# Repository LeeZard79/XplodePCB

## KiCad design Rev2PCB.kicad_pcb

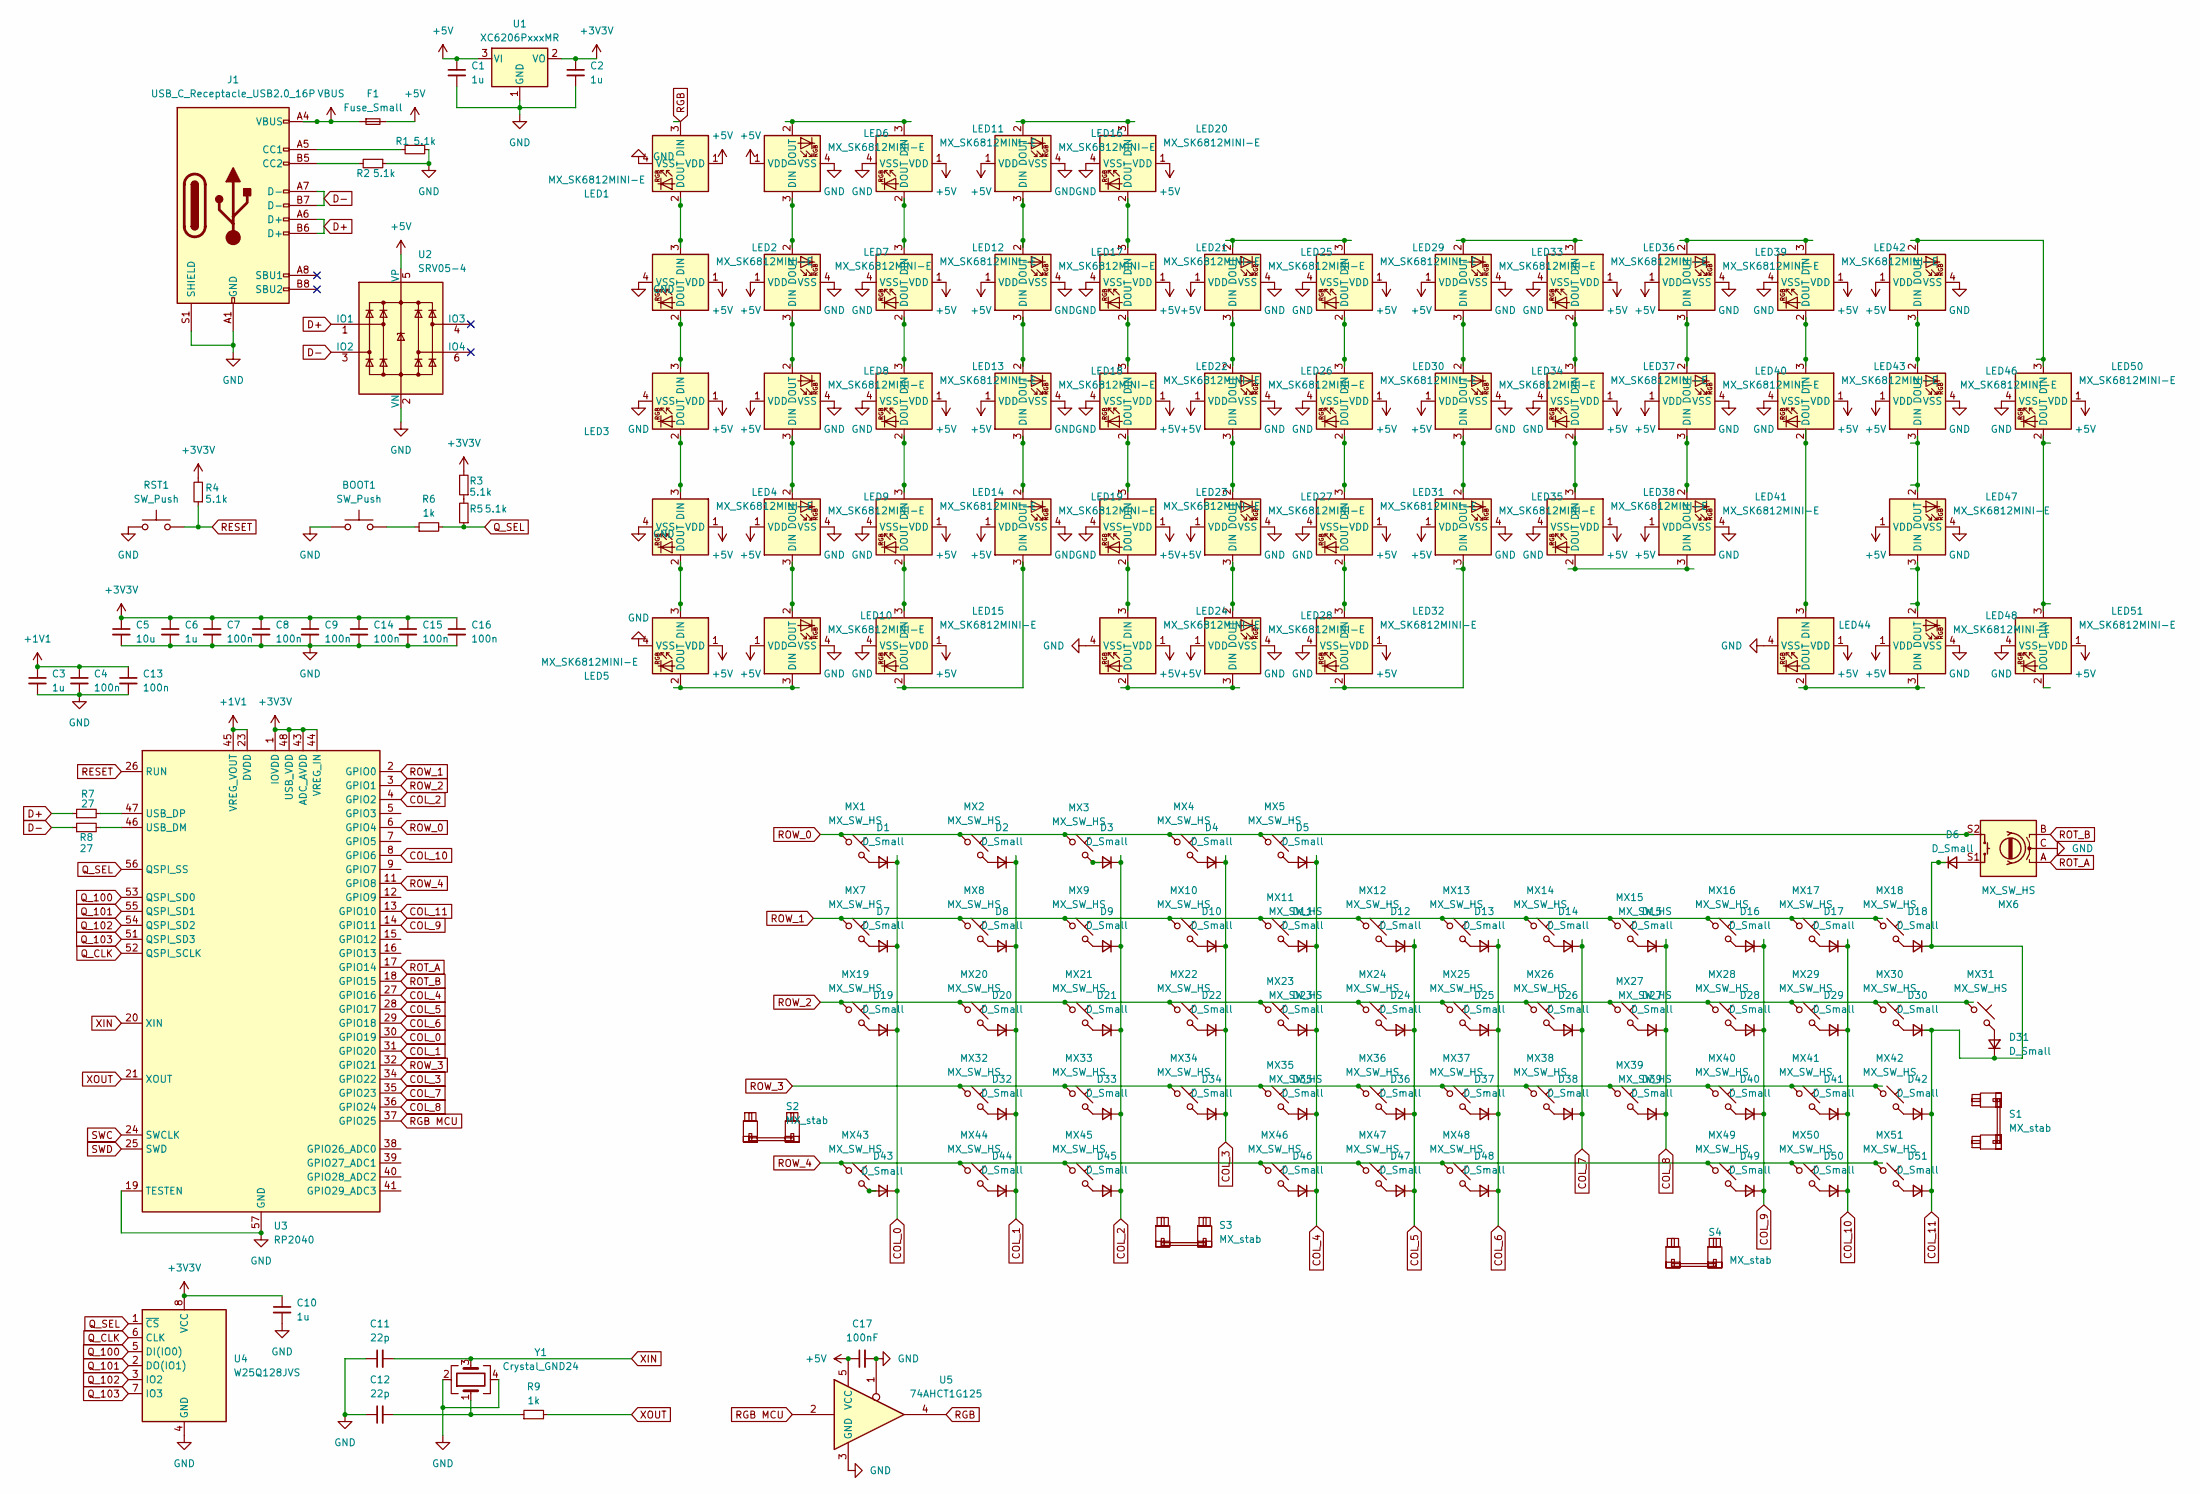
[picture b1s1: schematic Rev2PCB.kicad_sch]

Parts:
BOOT1: SW_Push; SW_SPST_TL3342
C1, C2, C3, C6, C10: 1u; C_0402_1005Metric
C4, C7, C8, C9, C13, C14, C15, C16: 100n; C_0402_1005Metric
C5: 10u; C_0603_1608Metric
C11, C12: 22p; C_0402_1005Metric
C17: 100nF; C_0402_1005Metric
D1, D2, D3, D4, D5, D6, D7, D8, D9, D10, D11, D12, D13, D14, D15, D16, D17, D18, D19, D20, D21, D22, D23, D24, D25, D26, D27, D28, D29, D30, D31, D32, D33, D34, D35, D36, D37, D38, D39, D40, D41, D42, D43, D44, D45, D46, D47, D48, D49, D50, D51: D_Small; D_SOD-123
F1: Fuse_Small; Fuse_1206_3216Metric
J1: USB_C_Receptacle_USB2.0_16P; USB_C_Receptacle_HRO_TYPE-C-31-M-12
LED1, LED2, LED3, LED4, LED5, LED6, LED7, LED8, LED9, LED10, LED11, LED12, LED13, LED14, LED15, LED16, LED17, LED18, LED19, LED20, LED21, LED22, LED23, LED24, LED25, LED26, LED27, LED28, LED29, LED30, LED31, LED32, LED33, LED34, LED35, LED36, LED37, LED38, LED39, LED40, LED41, LED42, LED43, LED44, LED45, LED46, LED47, LED48, LED50, LED51: MX_SK6812MINI-E; LED_MX_6028R
MX1, MX2, MX3, MX4, MX5, MX8, MX9, MX10, MX11, MX12, MX13, MX14, MX15, MX16, MX17, MX18, MX19, MX20, MX21, MX22, MX23, MX24, MX25, MX26, MX27, MX28, MX29, MX30, MX31, MX32, MX33, MX34, MX35, MX36, MX37, MX38, MX39, MX40, MX41, MX42, MX43, MX44, MX45, MX46, MX47, MX48, MX49, MX50, MX51: MX_SW_HS; SW_MX_HS_CPG151101S11_1u
MX6: MX_SW_HS; RotaryEncoder_Alps_EC11E-Switch_Vertical_H20mm
MX7: MX_SW_HS; SW_MX_HS_CPG151101S11_1.25u
R1, R2, R3, R4, R5: 5.1k; R_0402_1005Metric
R6, R9: 1k; R_0402_1005Metric
R7, R8: 27; R_0402_1005Metric
RST1: SW_Push; SW_SPST_TL3342
S1: MX_stab; STAB_MX_P_ISO
S2: MX_stab; STAB_MX_P_2u
S3, S4: MX_stab; STAB_MX_P_3u
U1: XC6206PxxxMR; SOT-23-3
U2: SRV05-4; SOT-23-6
U3: RP2040; QFN-56-1EP_7x7mm_P0.4mm_EP3.2x3.2mm
U4: W25Q128JVS; SOIC-8_5.23x5.23mm_P1.27mm
U5: 74AHCT1G125; SOT-23-5
Y1: Crystal_GND24; Crystal_SMD_3225-4Pin_3.2x2.5mm

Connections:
+1V1: C3.1, C4.1, C13.1, U3.23 (DVDD), U3.45 (VREG_VOUT), U3.50 (DVDD)
+3V3V: C2.1, C5.1, C6.1, C7.1, C8.1, C9.1, C10.1, C14.1, C15.1, C16.1, R3.2, R4.2, U1.2 (VO), U3.1 (IOVDD), U3.10 (IOVDD), U3.22 (IOVDD), U3.33 (IOVDD), U3.42 (IOVDD), U3.43 (ADC_AVDD), U3.44 (VREG_IN), U3.48 (USB_VDD), U3.49 (IOVDD), U4.8 (VCC)
+5V: C1.1, C17.1, F1.2, LED1.1 (VDD), LED2.1 (VDD), LED3.1 (VDD), LED4.1 (VDD), LED5.1 (VDD), LED6.1 (VDD), LED7.1 (VDD), LED8.1 (VDD), LED9.1 (VDD), LED10.1 (VDD), LED11.1 (VDD), LED12.1 (VDD), LED13.1 (VDD), LED14.1 (VDD), LED15.1 (VDD), LED16.1 (VDD), LED17.1 (VDD), LED18.1 (VDD), LED19.1 (VDD), LED20.1 (VDD), LED21.1 (VDD), LED22.1 (VDD), LED23.1 (VDD), LED24.1 (VDD), LED25.1 (VDD), LED26.1 (VDD), LED27.1 (VDD), LED28.1 (VDD), LED29.1 (VDD), LED30.1 (VDD), LED31.1 (VDD), LED32.1 (VDD), LED33.1 (VDD), LED34.1 (VDD), LED35.1 (VDD), LED36.1 (VDD), LED37.1 (VDD), LED38.1 (VDD), LED39.1 (VDD), LED40.1 (VDD), LED41.1 (VDD), LED42.1 (VDD), LED43.1 (VDD), LED44.1 (VDD), LED45.1 (VDD), LED46.1 (VDD), LED47.1 (VDD), LED48.1 (VDD), LED50.1 (VDD), LED51.1 (VDD), U1.3 (VI), U2.5 (VP), U5.5 (VCC)
COL_2: D3.1 (K), D9.1 (K), D21.1 (K), D33.1 (K), D45.1 (K), U3.4 (GPIO2)
COL_3: D4.1 (K), D10.1 (K), D22.1 (K), D34.1 (K), U3.34 (GPIO22)
COL_4: D5.1 (K), D11.1 (K), D23.1 (K), D35.1 (K), D46.1 (K), U3.27 (GPIO16)
COL_5: D12.1 (K), D24.1 (K), D36.1 (K), D47.1 (K), U3.28 (GPIO17)
COL_6: D13.1 (K), D25.1 (K), D37.1 (K), D48.1 (K), U3.29 (GPIO18)
COL_7: D14.1 (K), D26.1 (K), D38.1 (K), U3.35 (GPIO23)
COL_8: D15.1 (K), D27.1 (K), D39.1 (K), U3.36 (GPIO24)
COL_9: D16.1 (K), D28.1 (K), D40.1 (K), D49.1 (K), U3.14 (GPIO11)
COL_10: D17.1 (K), D29.1 (K), D41.1 (K), D50.1 (K), U3.8 (GPIO6)
COL_11: D6.1 (K), D18.1 (K), D30.1 (K), D31.1 (K), D42.1 (K), D51.1 (K), U3.13 (GPIO10)
D+: J1.A6 (D+), J1.B6 (D+), R7.1, U2.1 (IO1)
D-: J1.A7 (D-), J1.B7 (D-), R8.1, U2.3 (IO2)
GND: BOOT1.1, C1.2, C2.2, C3.2, C4.2, C5.2, C6.2, C7.2, C8.2, C9.2, C10.2, C11.1, C12.1, C13.2, C14.2, C15.2, C16.2, C17.2, J1.A1 (GND), J1.A12 (GND), J1.B1 (GND), J1.B12 (GND), J1.S1 (SHIELD), LED1.4 (VSS), LED2.4 (VSS), LED3.4 (VSS), LED4.4 (VSS), LED5.4 (VSS), LED6.4 (VSS), LED7.4 (VSS), LED8.4 (VSS), LED9.4 (VSS), LED10.4 (VSS), LED11.4 (VSS), LED12.4 (VSS), LED13.4 (VSS), LED14.4 (VSS), LED15.4 (VSS), LED16.4 (VSS), LED17.4 (VSS), LED18.4 (VSS), LED19.4 (VSS), LED20.4 (VSS), LED21.4 (VSS), LED22.4 (VSS), LED23.4 (VSS), LED24.4 (VSS), LED25.4 (VSS), LED26.4 (VSS), LED27.4 (VSS), LED28.4 (VSS), LED29.4 (VSS), LED30.4 (VSS), LED31.4 (VSS), LED32.4 (VSS), LED33.4 (VSS), LED34.4 (VSS), LED35.4 (VSS), LED36.4 (VSS), LED37.4 (VSS), LED38.4 (VSS), LED39.4 (VSS), LED40.4 (VSS), LED41.4 (VSS), LED42.4 (VSS), LED43.4 (VSS), LED44.4 (VSS), LED45.4 (VSS), LED46.4 (VSS), LED47.4 (VSS), LED48.4 (VSS), LED50.4 (VSS), LED51.4 (VSS), MX6.C, R1.1, R2.1, RST1.1, U1.1 (GND), U2.2 (VN), U3.19 (TESTEN), U3.57 (GND), U4.4 (GND), U5.1, U5.3 (GND), Y1.2, Y1.4
unnamed: BOOT1.2, R6.1
unnamed: C12.2, R9.1, Y1.1
unnamed: D1.2 (A), MX1.2
unnamed: D2.2 (A), MX2.2
unnamed: D3.2 (A), MX3.2
unnamed: D4.2 (A), MX4.2
unnamed: D5.2 (A), MX5.2
unnamed: D6.2 (A), MX6.S1
unnamed: D7.2 (A), MX7.2
unnamed: D8.2 (A), MX8.2
unnamed: D9.2 (A), MX9.2
unnamed: D10.2 (A), MX10.2
unnamed: D11.2 (A), MX11.2
unnamed: D12.2 (A), MX12.2
unnamed: D13.2 (A), MX13.2
unnamed: D14.2 (A), MX14.2
unnamed: D15.2 (A), MX15.2
unnamed: D16.2 (A), MX16.2
unnamed: D17.2 (A), MX17.2
unnamed: D18.2 (A), MX18.2
unnamed: D19.2 (A), MX19.2
unnamed: D20.2 (A), MX20.2
unnamed: D21.2 (A), MX21.2
unnamed: D22.2 (A), MX22.2
unnamed: D23.2 (A), MX23.2
unnamed: D24.2 (A), MX24.2
unnamed: D25.2 (A), MX25.2
unnamed: D26.2 (A), MX26.2
unnamed: D27.2 (A), MX27.2
unnamed: D28.2 (A), MX28.2
unnamed: D29.2 (A), MX29.2
unnamed: D30.2 (A), MX30.2
unnamed: D31.2 (A), MX31.2
unnamed: D32.2 (A), MX32.2
unnamed: D33.2 (A), MX33.2
unnamed: D34.2 (A), MX34.2
unnamed: D35.2 (A), MX35.2
unnamed: D36.2 (A), MX36.2
unnamed: D37.2 (A), MX37.2
unnamed: D38.2 (A), MX38.2
unnamed: D41.2 (A), MX41.2
unnamed: D42.2 (A), MX42.2
unnamed: D43.2 (A), MX43.2
unnamed: D44.2 (A), MX44.2
unnamed: D45.2 (A), MX45.2
unnamed: D46.2 (A), MX46.2
unnamed: D47.2 (A), MX47.2
unnamed: D48.2 (A), MX48.2
unnamed: D49.2 (A), MX49.2
unnamed: D50.2 (A), MX50.2
unnamed: D51.2 (A), MX51.2
unnamed: J1.A5 (CC1), R1.2
unnamed: J1.B5 (CC2), R2.2
unnamed: LED1.2 (DOUT), LED2.3 (DIN)
unnamed: LED2.2 (DOUT), LED3.3 (DIN)
unnamed: LED3.2 (DOUT), LED4.3 (DIN)
unnamed: LED4.2 (DOUT), LED5.3 (DIN)
unnamed: LED6.3 (DIN), LED7.2 (DOUT)
unnamed: LED7.3 (DIN), LED8.2 (DOUT)
unnamed: LED8.3 (DIN), LED9.2 (DOUT)
unnamed: LED5.2 (DOUT), LED10.3 (DIN)
unnamed: LED9.3 (DIN), LED10.2 (DOUT)
unnamed: LED6.2 (DOUT), LED11.3 (DIN)
unnamed: LED11.2 (DOUT), LED12.3 (DIN)
unnamed: LED12.2 (DOUT), LED13.3 (DIN)
unnamed: LED13.2 (DOUT), LED14.3 (DIN)
unnamed: LED14.2 (DOUT), LED15.3 (DIN)
unnamed: LED15.2 (DOUT), LED19.3 (DIN)
unnamed: LED16.3 (DIN), LED17.2 (DOUT)
unnamed: LED16.2 (DOUT), LED20.3 (DIN)
unnamed: LED17.3 (DIN), LED18.2 (DOUT)
unnamed: LED18.3 (DIN), LED19.2 (DOUT)
unnamed: LED20.2 (DOUT), LED21.3 (DIN)
unnamed: LED21.2 (DOUT), LED22.3 (DIN)
unnamed: LED22.2 (DOUT), LED23.3 (DIN)
unnamed: LED23.2 (DOUT), LED24.3 (DIN)
unnamed: LED24.2 (DOUT), LED28.3 (DIN)
unnamed: LED25.3 (DIN), LED26.2 (DOUT)
unnamed: LED25.2 (DOUT), LED29.3 (DIN)
unnamed: LED26.3 (DIN), LED27.2 (DOUT)
unnamed: LED27.3 (DIN), LED28.2 (DOUT)
unnamed: LED29.2 (DOUT), LED30.3 (DIN)
unnamed: LED30.2 (DOUT), LED31.3 (DIN)
unnamed: LED31.2 (DOUT), LED32.3 (DIN)
unnamed: LED32.2 (DOUT), LED35.3 (DIN)
unnamed: LED33.3 (DIN), LED34.2 (DOUT)
unnamed: LED33.2 (DOUT), LED36.3 (DIN)
unnamed: LED34.3 (DIN), LED35.2 (DOUT)
unnamed: LED36.2 (DOUT), LED37.3 (DIN)
unnamed: LED37.2 (DOUT), LED38.3 (DIN)
unnamed: LED38.2 (DOUT), LED41.3 (DIN)
unnamed: LED39.3 (DIN), LED40.2 (DOUT)
unnamed: LED39.2 (DOUT), LED42.3 (DIN)
unnamed: LED40.3 (DIN), LED41.2 (DOUT)
unnamed: LED42.2 (DOUT), LED43.3 (DIN)
unnamed: LED43.2 (DOUT), LED44.3 (DIN)
unnamed: LED44.2 (DOUT), LED48.3 (DIN)
unnamed: LED45.3 (DIN), LED46.2 (DOUT)
unnamed: LED45.2 (DOUT), LED50.3 (DIN)
unnamed: LED46.3 (DIN), LED47.2 (DOUT)
unnamed: LED47.3 (DIN), LED48.2 (DOUT)
unnamed: LED50.2 (DOUT), LED51.3 (DIN)
unnamed: R3.1, R5.2
unnamed: R8.2, U3.46 (USB_DM)
unnamed: R7.2, U3.47 (USB_DP)
Q_100: U3.53 (QSPI_SD0), U4.5 (DI(IO0))
Q_101: U3.55 (QSPI_SD1), U4.2 (DO(IO1))
Q_102: U3.54 (QSPI_SD2), U4.3 (IO2)
Q_103: U3.51 (QSPI_SD3), U4.7 (IO3)
Q_CLK: U3.52 (QSPI_SCLK), U4.6 (CLK)
Q_SEL: R5.1, R6.2, U3.56 (QSPI_SS), U4.1 (~CS)
RESET: R4.1, RST1.2, U3.26 (RUN)
RGB: LED1.3 (DIN), U5.4
RGB MCU: U3.37 (GPIO25), U5.2
ROT_A: MX6.A, U3.17 (GPIO14)
ROT_B: MX6.B, U3.18 (GPIO15)
ROW_0: MX1.1, MX2.1, MX3.1, MX4.1, MX5.1, MX6.S2, U3.6 (GPIO4)
ROW_1: MX7.1, MX8.1, MX9.1, MX10.1, MX11.1, MX12.1, MX13.1, MX14.1, MX15.1, MX16.1, MX17.1, MX18.1, U3.2 (GPIO0)
ROW_2: MX19.1, MX20.1, MX21.1, MX22.1, MX23.1, MX24.1, MX25.1, MX26.1, MX27.1, MX28.1, MX29.1, MX30.1, MX31.1, U3.3 (GPIO1)
ROW_3: MX32.1, MX33.1, MX34.1, MX35.1, MX36.1, MX37.1, MX38.1, MX39.1, MX40.1, MX41.1, MX42.1, U3.32 (GPIO21)
ROW_4: MX43.1, MX44.1, MX45.1, MX46.1, MX47.1, MX48.1, MX49.1, MX50.1, MX51.1, U3.11 (GPIO8)
SWC: U3.24 (SWCLK)
SWD: U3.25 (SWD)
VBUS: F1.1, J1.A4 (VBUS), J1.A9 (VBUS), J1.B4 (VBUS), J1.B9 (VBUS)
XIN: C11.2, U3.20 (XIN), Y1.3
XOUT: R9.2, U3.21 (XOUT)

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
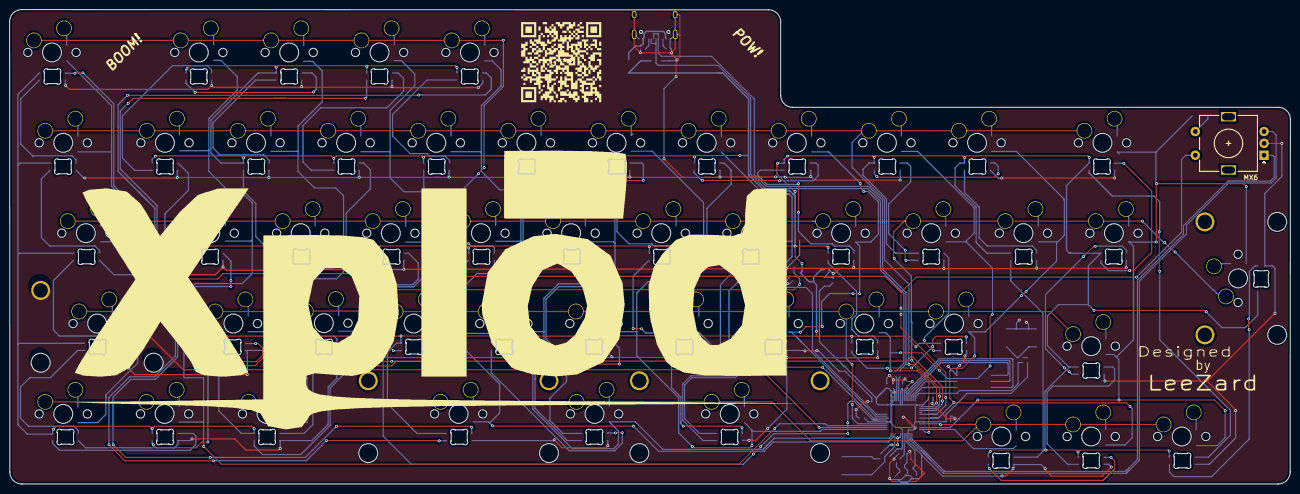
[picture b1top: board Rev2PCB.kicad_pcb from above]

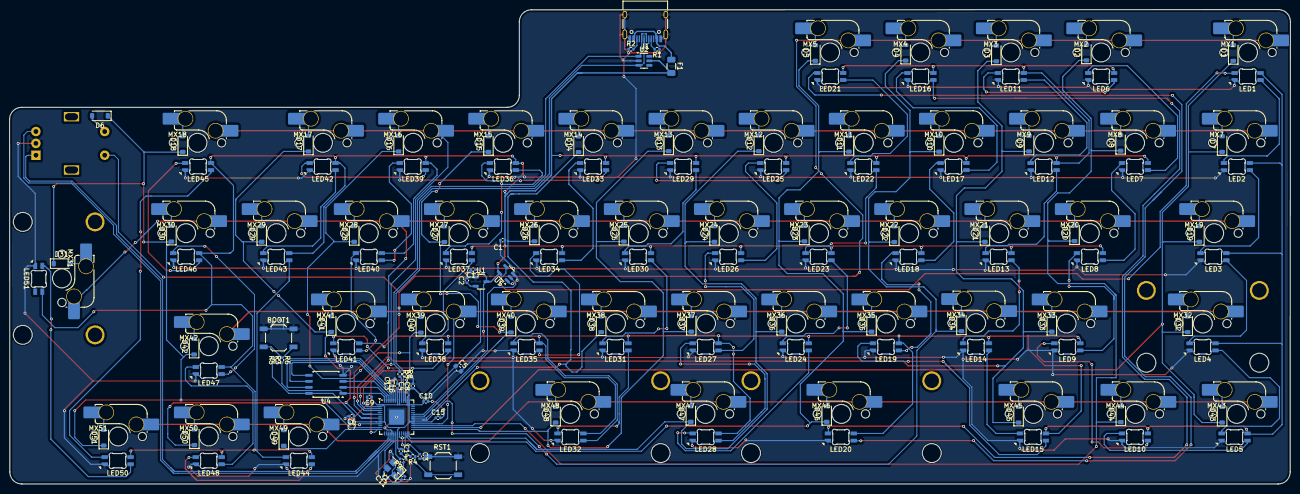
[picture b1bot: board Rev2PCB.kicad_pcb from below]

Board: 2 copper layers, 270.0 x 100.0 mm, 192 parts (187 on the bottom side), 144 nets.
